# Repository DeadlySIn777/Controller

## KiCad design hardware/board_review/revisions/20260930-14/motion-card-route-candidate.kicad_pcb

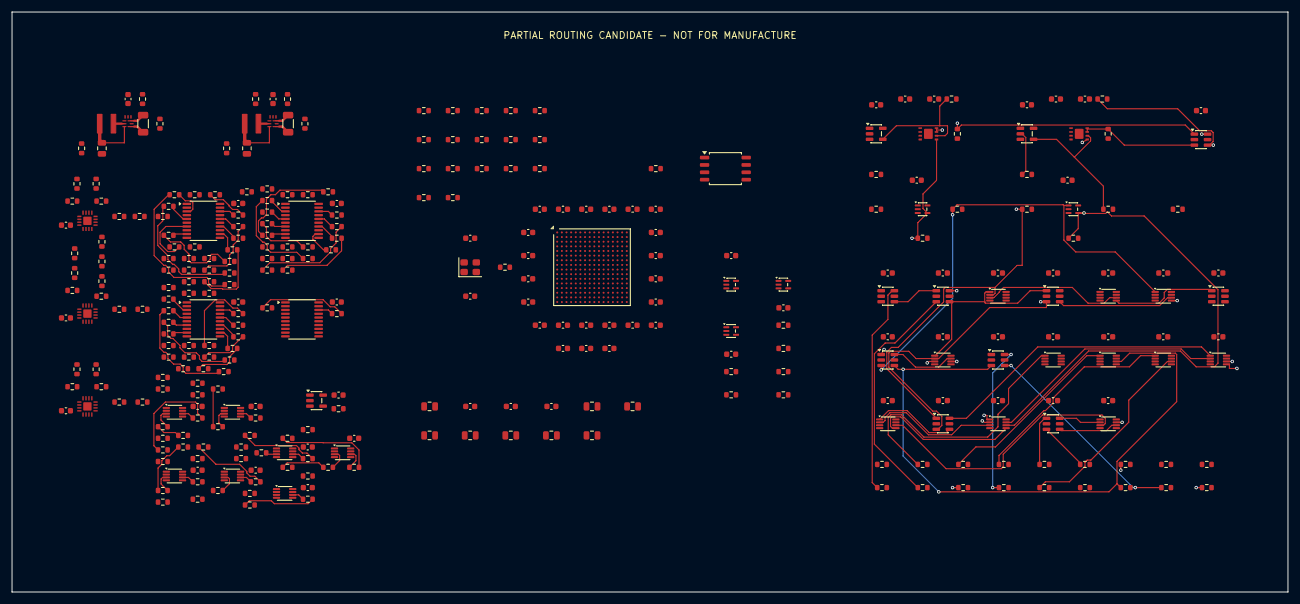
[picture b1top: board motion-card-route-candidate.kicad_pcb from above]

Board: 6 copper layers, 220.0 x 100.0 mm, 327 parts (0 on the bottom side), 203 nets.

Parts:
C1001, C1002, C1003, C1004, C1005, C1006, C1007, C1008, C1009, C1010, C1011, C1012, C1013, C1014, C1015, C1016, C1017, C1018, C1019, C1020, C1021, C1022, C1023, C1035, C1038: 885012206046; C_0603_1608Metric
C1024, C1028, C1029, C1030, C1031, C1032, C1033, C1034: 885012207053; C_0805_2012Metric
C1025, C1026, C1027, C1036, C1039: 885012206052; C_0603_1608Metric
C1037: 885012206040; C_0603_1608Metric
C2001, C2004: C3216X7R1E106K160AB; C_1206_3216Metric
C2002, C2005: C2012X7S1A226M125AC; C_0805_2012Metric
C2003, C2006: GRM1885C1H682JA01D; C_0603_1608Metric
C2007, C2008, C2009, C2010, C3003, C3004, C3005, C3006, C3007, C3008, C3009, C4001, C4002, C4003, C4004, C4005, C4006, C4007, C4008, C4009, C4010, C4011, C4012, C4013, C4014, C4015, C4016, C4017, C4018, C4019, C5001, C5002, C5003, C5004, C5005, C5006, C5007, C5008, C5009, C5010, C5011: GRM188R72A104KA35D; C_0603_1608Metric
C3001, C3002: CL10C332JB8NNNC; C_0603_1608Metric
L2001: XGL4020-222MEC; XGL4020
L2002: XGL4020-102MEC; XGL4020
R1001, R1002, R5001, R5002, R5003, R5004, R5005, R5006, R5007, R5008, R5009, R5010, R5011, R5012, R5013, R5014, R5015, R5016, R5017, R5018, R5019, R5020, R5021, R5022, R5023, R5024, R5025, R5026, R5027, R5028, R5029, R5030, R5031, R5032, R5033, R5034, R5035, R5036, R5037, R5038: CRCW060333R0FKEA; R_0603_1608Metric
R1003, R1004, R1005, R1006, R1007, R1008, R1009, R1010, R1011, R1012, R1013, R1014, R1015, R1016, R1017, R1018, R1019, R1022, R1023, R1024, R1025, R2002, R2006, R2103, R2105, R3001, R3002, R4008, R4009, R4010, R4011, R4012, R4013, R4014, R4015, R4016, R4017, R4018, R5077, R5078, R5079, R5080, R5081, R5082, R5083, R5084, R5085, R5086, R5087, R5088, R5089, R5090, R5091, R5092, R5093, R5094, R5095, R5096, R5097, R5098, R5099, R5100, R5101, R5102: CRCW060310K0FKEA; R_0603_1608Metric
R1020, R2106: CRCW060347K0FKEA; R_0603_1608Metric
R1021: CRCW06031K00FKEA; R_0603_1608Metric
R2001: CRCW060376K8FKEA; R_0603_1608Metric
R2003, R2007, R3006, R3008, R3009, R3010, R3011, R3012: CRCW0603100KFKEA; R_0603_1608Metric
R2005: CRCW060332K4FKEA; R_0603_1608Metric
R2008: CRCW0603301KFKEA; R_0603_1608Metric
R2021: PLT0603Z8792LST1; R_0603_1608Metric
R2027, R2035, R2067, R2075: PLT0603Z1002LST1; R_0603_1608Metric
R2029: PLT0603Z9212LST1; R_0603_1608Metric
R2041: PLT0603Z1071LST1; R_0603_1608Metric
R2042: PLT0603Z2610LST1; R_0603_1608Metric
R2047, R2055: PLT0603Z1001LST1; R_0603_1608Metric
R2049: PLT0603Z1151LST1; R_0603_1608Metric
R2050: PLT0603Z3160LST1; R_0603_1608Metric
R2051: CRCW06034R02FKEA; R_0603_1608Metric
R2061: PLT0603Z5452LST1; R_0603_1608Metric
R2069: PLT0603Z5752LST1; R_0603_1608Metric
R2101, R2102: CRCW06033K30FKEA; R_0603_1608Metric
R2104: CRCW06036K80FKEA; R_0603_1608Metric
R2107: CRCW0603470KFKEA; R_0603_1608Metric
R2108, R3003, R3004, R3005, R3007, R3013, R4001, R4002, R4003, R4004, R4005, R4006, R4007, R5039, R5040, R5041, R5042, R5043, R5044, R5045, R5046, R5047, R5048, R5049, R5050, R5051, R5052, R5053, R5054, R5055, R5056, R5057, R5058, R5059, R5060, R5061, R5062, R5063, R5064, R5065, R5066, R5067, R5068, R5069, R5070, R5071, R5072, R5073, R5074, R5075, R5076: CRCW06034K70FKEA; R_0603_1608Metric
U1001: T20F256I4; T20F256_Efinix_NSMD
U1002: W25Q32JVSSIQ; SOIC-8_5.3x5.3mm_P1.27mm
U1003, U1005, U3006, U3007: SN74LVC1G08DCKR; SOT-353_SC-70-5
U1004: 74LVC1G17GW; SOT-353_SC-70-5
U2001, U2002: TPS62901RPJR; TPS62901_RPJ9
U2003, U2004, U2005: LTC2962HUD#PBF; LTC2962_UD16
U2006: SN74LVC1G17DBVR; SOT-23-5
U3001, U3002: TPS3851G18SDRBT; TPS3851_DRB8
U3003, U3004: SN74LVC1G34DBVR; SOT-23-5
U3005: SN74LVC2G17DBVR; SOT-23-6
U4001, U4002, U4004, U4007, U4008, U4010: SN74LVC1G11DBVR; SOT-23-6
U4003, U4009, U4019: SN74LVC2G08DCUR; VSSOP-8_2.3x2mm_P0.5mm
U4005, U4006, U4011, U4012, U4013, U4014, U4015: SN74LVC2G74DCUR; VSSOP-8_2.3x2mm_P0.5mm
U4016, U4018: SN74LVC2G04DBVR; SOT-23-6
U4017: SN74LVC2G32DCUR; VSSOP-8_2.3x2mm_P0.5mm
U5001, U5002, U5003, U5004: SN74LVC244APWR; TSSOP-20_4.4x6.5mm_P0.65mm
U5005, U5006, U5007, U5008, U5009, U5010, U5011: SN74LVC2G126DCUR; VSSOP-8_2.3x2mm_P0.5mm
Y1001: ASE-50.000MHZ-L-C-T; Oscillator_SMD_Abracon_ASE-4Pin_3.2x2.5mm

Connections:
/BANK_B_BUFFER_ENABLE_QUALIFIED: R4014.1, R5076.1, U4013.6, U5005.1, U5005.7, U5006.1, U5006.7, U5007.1, U5007.7, U5008.1, U5008.7, U5009.1, U5009.7, U5010.1, U5010.7, U5011.1
/CORE_1V2: C1001.1, C1002.1, C1003.1, C1004.1, C1005.1, C1006.1, C1007.1, C1008.1, C1009.1, C1024.1, C1025.1, C1026.1, C1027.1, C2002.1, L2001.2, R2003.1, R2041.1, R2049.1, U1001.E9, U1001.F7, U1001.F8, U1001.F9, U1001.G11, U1001.J6, U1001.J7, U1001.K9, U1001.K11, U2001.3
/DIR0_FPGA: R5040.1, U1001.J5, U5001.4
/DIR1_FPGA: R5042.1, U1001.K3, U5001.11
/DIR2_FPGA: R5044.1, U1001.K1, U5001.17
/DIR3_FPGA: R5046.1, U1001.H1, U5002.6
/DIR4_FPGA: R5048.1, U1001.H2, U5002.13
/DIR5_FPGA: R5050.1, U1001.G3, U5003.2
/DIR6_FPGA: R5052.1, U1001.G2, U5003.8
/DIR7_FPGA: R5054.1, U1001.C1, U5003.15
/DIR8_FPGA: R5056.1, U1001.F3, U5005.5
/DIR9_FPGA: R5058.1, U1001.E1, U5007.2
/DIR10_FPGA: R5060.1, U1001.G4, U5008.5
/DIR11_FPGA: R5062.1, U1001.B1, U5010.2
/EN0_N_FPGA: R5063.1, U1001.H12, U5001.6
/EN1_N_FPGA: R5064.1, U1001.J12, U5001.13
/EN2_N_FPGA: R5065.1, U1001.L16, U5002.2
/EN3_N_FPGA: R5066.1, U1001.M15, U5002.8
/EN4_N_FPGA: R5067.1, U1001.M16, U5002.15
/EN5_N_FPGA: R5068.1, U1001.P16, U5003.4
/EN6_N_FPGA: R5069.1, U1001.L15, U5003.11
/EN7_N_FPGA: R5070.1, U1001.K12, U5003.17
/EN8_N_FPGA: R5071.1, U1001.N14, U5006.2
/EN9_N_FPGA: R5072.1, U1001.N16, U5007.5
/EN10_N_FPGA: R5073.1, U1001.P15, U5009.2
/EN11_N_FPGA: R5074.1, U1001.M14, U5010.5
/FPGA_CRESET_N: R2108.1, R4008.1, U1003.1, U2006.4, U4001.1, U4019.1, U4019.5
/FPGA_ENDPOINT_READY: R1023.1, R4001.1, U1001.C4, U4003.6, U4004.6
/FPGA_MOTION_REQUEST: R1024.1, R3003.1, U1001.B3, U3006.1, U4005.1, U4007.3
/FPGA_OUTPUT_REQUEST: R3004.1, U3007.1, U4006.1, U4008.3
/FPGA_PROGRESS_M: R1025.1, R3005.1, U1001.E4, U3003.2
/FPGA_USER_RESET_N: R3013.1, R4009.1, U1001.D5, U1005.4, U3006.2, U3007.2, U4001.3
/IO_3V3: C1010.1, C1011.1, C1012.1, C1013.1, C1014.1, C1015.1, C1016.1, C1017.1, C1018.1, C1019.1, C1020.1, C1021.1, C1022.1, C1023.1, C1028.1, C1029.1, C1030.1, C1031.1, C1032.1, C1033.1, C1034.1, C1035.1, C1036.1, C1037.1, C1038.1, C2005.1, C2010.1, C3003.1, C3004.1, C3005.1, C3006.1, C3007.1, C3008.1, C3009.1, C4001.1, C4002.1, C4003.1, C4004.1, C4005.1, C4006.1, C4007.1, C4008.1, C4009.1, C4010.1, C4011.1, C4012.1, C4013.1, C4014.1, C4015.1, C4016.1, C4017.1, C4018.1, C4019.1, C5001.1, C5002.1, C5003.1, C5004.1, C5005.1, C5006.1, C5007.1, C5008.1, C5009.1, C5010.1, C5011.1, L2002.2, R1003.1, R1004.1, R1005.1, R1006.1, R1007.1, R1008.1, R1009.1, R1010.1, R1011.1, R1012.1, R1013.1, R1014.1, R1015.1, R1016.1, R1017.1, R1020.1, R2007.1, R2061.1, R2069.1, R3001.1, R3002.1, R5063.2, R5064.2, R5065.2, R5066.2, R5067.2, R5068.2, R5069.2, R5070.2, R5071.2, R5072.2, R5073.2, R5074.2, U1001.E10, U1001.F6, U1001.F10, U1001.F11, U1001.G6, U1001.H6, U1001.H7, U1001.J10, U1001.J11, U1001.K6, U1001.L6, U1001.L7, U1001.L10, U1001.L11, U1002.8, U1003.5, U1004.5, U1005.5, U2002.3, U2006.5, U3001.1, U3002.1, U3003.5, U3004.5, U3005.5, U3006.5, U3007.5, U4001.5, U4002.5, U4003.8, U4004.5, U4005.2, U4005.7, U4005.8, U4006.2, U4006.7, U4006.8, U4007.5, U4008.5, U4009.8, U4010.5, U4011.2, U4011.7, U4011.8, U4012.2, U4012.7, U4012.8, U4013.2, U4013.7, U4013.8, U4014.7, U4014.8, U4015.7, U4015.8, U4016.5, U4017.8, U4018.5, U4019.8, U5001.20, U5002.20, U5003.20, U5004.20, U5005.8, U5006.8, U5007.8, U5008.8, U5009.8, U5010.8, U5011.8, Y1001.1, Y1001.4
/LOGIC_GND: C1001.2, C1002.2, C1003.2, C1004.2, C1005.2, C1006.2, C1007.2, C1008.2, C1009.2, C1010.2, C1011.2, C1012.2, C1013.2, C1014.2, C1015.2, C1016.2, C1017.2, C1018.2, C1019.2, C1020.2, C1021.2, C1022.2, C1023.2, C1024.2, C1025.2, C1026.2, C1027.2, C1028.2, C1029.2, C1030.2, C1031.2, C1032.2, C1033.2, C1034.2, C1035.2, C1036.2, C1037.2, C1038.2, C1039.2, C2001.2, C2002.2, C2003.2, C2004.2, C2005.2, C2006.2, C2007.2, C2008.2, C2009.2, C2010.2, C3001.2, C3002.2, C3003.2, C3004.2, C3005.2, C3006.2, C3007.2, C3008.2, C3009.2, C4001.2, C4002.2, C4003.2, C4004.2, C4005.2, C4006.2, C4007.2, C4008.2, C4009.2, C4010.2, C4011.2, C4012.2, C4013.2, C4014.2, C4015.2, C4016.2, C4017.2, C4018.2, C4019.2, C5001.2, C5002.2, C5003.2, C5004.2, C5005.2, C5006.2, C5007.2, C5008.2, C5009.2, C5010.2, C5011.2, R1018.2, R1019.2, R1021.2, R1023.2, R1024.2, R1025.2, R2001.2, R2002.2, R2003.2, R2005.2, R2006.2, R2007.2, R2008.2, R2027.2, R2035.2, R2047.2, R2055.2, R2067.2, R2075.2, R2103.2, R2105.2, R2107.2, R2108.2, R3003.2, R3004.2, R3005.2, R3006.2, R3007.2, R3008.2, R3009.2, R3010.2, R3011.2, R3012.2, R3013.2, R4001.2, R4002.2, R4003.2, R4004.2, R4005.2, R4006.2, R4007.2, R4008.2, R4009.2, R4010.2, R4011.2, R4012.2, R4013.2, R4014.2, R4015.2, R4016.2, R4017.2, R4018.2, R5039.2, R5040.2, R5041.2, R5042.2, R5043.2, R5044.2, R5045.2, R5046.2, R5047.2, R5048.2, R5049.2, R5050.2, R5051.2, R5052.2, R5053.2, R5054.2, R5055.2, R5056.2, R5057.2, R5058.2, R5059.2, R5060.2, R5061.2, R5062.2, R5075.2, R5076.2, R5077.2, R5078.2, R5079.2, R5080.2, R5081.2, R5082.2, R5083.2, R5084.2, R5085.2, R5086.2, R5087.2, R5088.2, R5089.2, R5090.2, R5091.2, R5092.2, R5093.2, R5094.2, R5095.2, R5096.2, R5097.2, R5098.2, R5099.2, R5100.2, R5101.2, R5102.2, U1001.A1, U1001.A5, U1001.A12, U1001.A16, U1001.D2, U1001.D15, U1001.G7, U1001.G8, U1001.G9, U1001.G10, U1001.H8, U1001.H9, U1001.H10, U1001.H11, U1001.J1, U1001.J8, U1001.J9, U1001.J16, U1001.K7, U1001.K8, U1001.K10, U1001.L8, U1001.L9, U1001.N2, U1001.N15, U1001.R7, U1001.R10, U1001.T1, U1001.T4, U1001.T13, U1001.T16, U1002.4, U1003.3, U1004.3, U1005.3, U2001.4, U2001.9, U2002.4, U2003.3, U2003.7, U2003.11, U2003.17, U2004.3, U2004.7, U2004.11, U2004.17, U2005.3, U2005.7, U2005.11, U2005.17, U2006.3, U3001.4, U3001.9, U3002.4, U3002.9, U3003.3, U3004.3, U3005.2, U3006.3, U3007.3, U4001.2, U4002.2, U4003.4, U4004.2, U4005.4, U4006.4, U4007.2, U4008.2, U4009.4, U4010.2, U4011.4, U4012.4, U4013.4, U4014.4, U4015.4, U4016.2, U4017.4, U4018.2, U4019.4, U5001.1, U5001.10, U5001.19, U5002.1, U5002.10, U5002.19, U5003.1, U5003.10, U5003.19, U5004.1, U5004.4, U5004.6, U5004.8, U5004.10, U5004.11, U5004.13, U5004.15, U5004.17, U5004.19, U5005.4, U5006.4, U5007.4, U5008.4, U5009.4, U5010.4, U5011.4, U5011.5, U5011.7, Y1001.2
/RAW_INHIBIT_N: U1001.A2, U4003.5, U4003.7, U4007.6
/STEP0_FPGA: R5039.1, U1001.P2, U5001.2
/STEP1_FPGA: R5041.1, U1001.J4, U5001.8
/STEP2_FPGA: R5043.1, U1001.J3, U5001.15
/STEP3_FPGA: R5045.1, U1001.K2, U5002.4
/STEP4_FPGA: R5047.1, U1001.L1, U5002.11
/STEP5_FPGA: R5049.1, U1001.H4, U5002.17
/STEP6_FPGA: R5051.1, U1001.G5, U5003.6
/STEP7_FPGA: R5053.1, U1001.F1, U5003.13
/STEP8_FPGA: R5055.1, U1001.E2, U5005.2
/STEP9_FPGA: R5057.1, U1001.D1, U5006.5
/STEP10_FPGA: R5059.1, U1001.E3, U5008.2
/STEP11_FPGA: R5061.1, U1001.F4, U5009.5
/TX_PERMIT: R4015.1, R5075.1, U1001.E6, U4007.4, U4009.5, U4010.1, U4011.6, U5004.2, U5011.2
/WD_M_OK: R3009.1, U3005.6, U4003.2, U4016.1
/WD_M_SET1_BUF: R3011.1, U3001.5, U3006.4, U4017.2
/WD_O_OK: R3010.1, U3005.4, U4004.3, U4009.2, U4016.3
/WD_O_SET1_BUF: R3012.1, U3002.5, U3007.4, U4017.6
/fpga_core/FPGA_CDONE: R1003.2, R1022.1, U1001.R1
/fpga_core/FPGA_CFG_CBSEL0: R1018.1, U1001.C7
/fpga_core/FPGA_CFG_CBSEL1: R1019.1, U1001.D7
/fpga_core/FPGA_CFG_CBUS0: R1009.2, U1001.K13
/fpga_core/FPGA_CFG_CBUS1: R1008.2, U1001.L14
/fpga_core/FPGA_CFG_CBUS2: R1007.2, U1001.R16
/fpga_core/FPGA_CFG_CSI: R1004.2, U1001.N3
/fpga_core/FPGA_CFG_NSTATUS: R1017.2, U1001.B8
/fpga_core/FPGA_CFG_TEST_N: R1005.2, U1001.L12
/fpga_core/FPGA_CLK_50M: R1001.2, U1001.H3
/fpga_core/FPGA_CLK_SOURCE: R1001.1, Y1001.3
/fpga_core/FPGA_FLASH_CCK: R1002.2, U1002.6
/fpga_core/FPGA_FLASH_CCK_SOURCE: R1002.1, U1001.M3
/fpga_core/FPGA_FLASH_CS_N: R1006.2, U1001.P3, U1002.1
/fpga_core/FPGA_FLASH_IO2: R1014.2, U1002.3
/fpga_core/FPGA_FLASH_IO3: R1015.2, U1002.7
/fpga_core/FPGA_FLASH_MISO: U1001.N1, U1002.2
/fpga_core/FPGA_FLASH_MOSI: U1001.L3, U1002.5
/fpga_core/FPGA_JTAG_TCK: R1010.2, U1001.M2
/fpga_core/FPGA_JTAG_TDI: R1011.2, U1001.K5
/fpga_core/FPGA_JTAG_TDO: R1013.2, U1001.L5
/fpga_core/FPGA_JTAG_TMS: R1012.2, U1001.M1
/fpga_core/FPGA_LOCAL_RESET_N: R1020.2, R1021.1, U1001.P1, U1003.4
/fpga_core/FPGA_SERVICE_RUN_N: R1016.2, U1003.2, U1005.2
/fpga_core/FPGA_USER_RESET_DELAYED: U1004.4, U1005.1
/fpga_core/FPGA_USER_RESET_RC: C1039.1, R1022.2, U1004.2
/mc_local_power/CORE_1V2_EN: R2002.1, R2102.2, R2103.1, U2001.5
/mc_local_power/CORE_1V2_MODE: R2001.1, U2001.7
/mc_local_power/CORE_1V2_OV_SENSE: R2051.2, R2055.1, U2004.15
/mc_local_power/CORE_1V2_SS: C2003.1, U2001.8
/mc_local_power/CORE_1V2_SW: L2001.1, U2001.2
/mc_local_power/CORE_1V2_UV_SENSE: R2042.2, R2047.1, U2004.16
/mc_local_power/CORE_5V: C2001.1, C2004.1, C2007.1, C2008.1, C2009.1, R2021.1, R2029.1, R2101.1, R2104.1, R2106.1, U2001.6, U2002.6, U2003.1, U2003.2, U2003.4, U2003.10, U2003.13, U2003.14, U2004.1, U2004.4, U2004.10, U2004.13, U2004.14, U2005.1, U2005.4, U2005.10, U2005.13, U2005.14
/mc_local_power/CORE_5V_OV_SENSE: R2029.2, R2035.1, U2003.15
/mc_local_power/CORE_5V_UV_SENSE: R2021.2, R2027.1, U2003.16
/mc_local_power/IO_3V3_EN: R2006.1, R2104.2, R2105.1, U2002.5, U2004.12, U2005.2
/mc_local_power/IO_3V3_MODE: R2005.1, U2002.7
/mc_local_power/IO_3V3_OV_SENSE: R2069.2, R2075.1, U2005.15
/mc_local_power/IO_3V3_SS: C2006.1, U2002.8
/mc_local_power/IO_3V3_SW: L2002.1, U2002.2
/mc_local_power/IO_3V3_UV_SENSE: R2061.2, R2067.1, U2005.16
/mc_local_power/IO_3V3_VSET: R2008.1, U2002.9
/mc_local_power/MC_RAILS_OK_5V: R2106.2, R2107.1, U2005.12, U2006.2
/mc_local_power/MC_SEQ_5V_OK: R2101.2, R2102.1, U2003.12, U2004.2
/mc_local_power/MC_SEQ_OV2_1: R2049.2, R2050.1
/mc_local_power/MC_SEQ_OV2_2: R2050.2, R2051.1
/mc_local_power/MC_SEQ_REF1: U2003.5, U2003.6, U2003.8, U2003.9
/mc_local_power/MC_SEQ_REF2: U2004.5, U2004.6, U2004.8, U2004.9
/mc_local_power/MC_SEQ_REF3: U2005.5, U2005.6, U2005.8, U2005.9
/mc_local_power/MC_SEQ_UV2_1: R2041.2, R2042.1
/mc_motor_buffers/DIR0_BUFFER_OUT: R5002.1, U5001.16
/mc_motor_buffers/DIR0_TO_MIA: R5002.2, R5078.1
/mc_motor_buffers/DIR1_BUFFER_OUT: R5005.1, U5001.9
/mc_motor_buffers/DIR1_TO_MIA: R5005.2, R5080.1
/mc_motor_buffers/DIR2_BUFFER_OUT: R5008.1, U5001.3
/mc_motor_buffers/DIR2_TO_MIA: R5008.2, R5082.1
/mc_motor_buffers/DIR3_BUFFER_OUT: R5011.1, U5002.14
/mc_motor_buffers/DIR3_TO_MIA: R5011.2, R5084.1
/mc_motor_buffers/DIR4_BUFFER_OUT: R5014.1, U5002.7
/mc_motor_buffers/DIR4_TO_MIA: R5014.2, R5086.1
/mc_motor_buffers/DIR5_BUFFER_OUT: R5017.1, U5003.18
/mc_motor_buffers/DIR5_TO_MIA: R5017.2, R5088.1
/mc_motor_buffers/DIR6_BUFFER_OUT: R5020.1, U5003.12
/mc_motor_buffers/DIR6_TO_MIA: R5020.2, R5090.1
/mc_motor_buffers/DIR7_BUFFER_OUT: R5023.1, U5003.5
/mc_motor_buffers/DIR7_TO_MIA: R5023.2, R5092.1
/mc_motor_buffers/DIR8_BUFFER_OUT: R5026.1, U5005.3
/mc_motor_buffers/DIR8_TO_MX4: R5026.2, R5094.1
/mc_motor_buffers/DIR9_BUFFER_OUT: R5029.1, U5007.6
/mc_motor_buffers/DIR9_TO_MX4: R5029.2, R5096.1
/mc_motor_buffers/DIR10_BUFFER_OUT: R5032.1, U5008.3
/mc_motor_buffers/DIR10_TO_MX4: R5032.2, R5098.1
/mc_motor_buffers/DIR11_BUFFER_OUT: R5035.1, U5010.6
/mc_motor_buffers/DIR11_TO_MX4: R5035.2, R5100.1
/mc_motor_buffers/EN0_N_BUFFER_OUT: R5003.1, U5001.14
/mc_motor_buffers/EN1_N_BUFFER_OUT: R5006.1, U5001.7
/mc_motor_buffers/EN2_N_BUFFER_OUT: R5009.1, U5002.18
/mc_motor_buffers/EN3_N_BUFFER_OUT: R5012.1, U5002.12
/mc_motor_buffers/EN4_N_BUFFER_OUT: R5015.1, U5002.5
/mc_motor_buffers/EN5_N_BUFFER_OUT: R5018.1, U5003.16
/mc_motor_buffers/EN6_N_BUFFER_OUT: R5021.1, U5003.9
/mc_motor_buffers/EN7_N_BUFFER_OUT: R5024.1, U5003.3
/mc_motor_buffers/EN8_N_BUFFER_OUT: R5027.1, U5006.6
/mc_motor_buffers/EN9_N_BUFFER_OUT: R5030.1, U5007.3
/mc_motor_buffers/EN10_N_BUFFER_OUT: R5033.1, U5009.6
/mc_motor_buffers/EN11_N_BUFFER_OUT: R5036.1, U5010.3
/mc_motor_buffers/STEP0_BUFFER_OUT: R5001.1, U5001.18
/mc_motor_buffers/STEP0_TO_MIA: R5001.2, R5077.1
/mc_motor_buffers/STEP1_BUFFER_OUT: R5004.1, U5001.12
/mc_motor_buffers/STEP1_TO_MIA: R5004.2, R5079.1
/mc_motor_buffers/STEP2_BUFFER_OUT: R5007.1, U5001.5
/mc_motor_buffers/STEP2_TO_MIA: R5007.2, R5081.1
/mc_motor_buffers/STEP3_BUFFER_OUT: R5010.1, U5002.16
/mc_motor_buffers/STEP3_TO_MIA: R5010.2, R5083.1
/mc_motor_buffers/STEP4_BUFFER_OUT: R5013.1, U5002.9
/mc_motor_buffers/STEP4_TO_MIA: R5013.2, R5085.1
/mc_motor_buffers/STEP5_BUFFER_OUT: R5016.1, U5002.3
/mc_motor_buffers/STEP5_TO_MIA: R5016.2, R5087.1
/mc_motor_buffers/STEP6_BUFFER_OUT: R5019.1, U5003.14
/mc_motor_buffers/STEP6_TO_MIA: R5019.2, R5089.1
/mc_motor_buffers/STEP7_BUFFER_OUT: R5022.1, U5003.7
/mc_motor_buffers/STEP7_TO_MIA: R5022.2, R5091.1
/mc_motor_buffers/STEP8_BUFFER_OUT: R5025.1, U5005.6
/mc_motor_buffers/STEP8_TO_MX4: R5025.2, R5093.1
/mc_motor_buffers/STEP9_BUFFER_OUT: R5028.1, U5006.3
/mc_motor_buffers/STEP9_TO_MX4: R5028.2, R5095.1
/mc_motor_buffers/STEP10_BUFFER_OUT: R5031.1, U5008.6
/mc_motor_buffers/STEP10_TO_MX4: R5031.2, R5097.1
/mc_motor_buffers/STEP11_BUFFER_OUT: R5034.1, U5009.3
/mc_motor_buffers/STEP11_TO_MX4: R5034.2, R5099.1
/mc_motor_buffers/TX_PERMIT_A_BUFFER_OUT: R5037.1, U5004.18
/mc_motor_buffers/TX_PERMIT_A_TO_MIA: R5037.2, R5101.1
/mc_motor_buffers/TX_PERMIT_B_BUFFER_OUT: R5038.1, U5011.6
/mc_motor_buffers/TX_PERMIT_B_TO_MX4: R5038.2, R5102.1
/mc_permission/ARM_M_Q: U4005.5, U4007.1
/mc_permission/ARM_O_Q: U4006.5, U4008.1
/mc_permission/BASE_FIRST: U4001.4, U4002.1
/mc_permission/BASE_OK: U4002.4, U4003.1, U4004.1, U4009.1
/mc_permission/DIC_OK_QUALIFIED: R4010.1, U4001.6
/mc_permission/EXT_PERMIT_3V3: R4011.1, U4002.3
/mc_permission/LATCH_CLEAR_M_N: U4003.3, U4005.6
/mc_permission/LATCH_CLEAR_O_N: U4004.4, U4006.6
/mc_permission/OPI_REARM_BOE: R4004.1, U4013.1
/mc_permission/OPI_REARM_OUT: R4003.1, U4012.1
/mc_permission/OPI_REARM_TX: R4002.1, U4011.1
/mc_permission/OUTPUT_RAW_OK: U4008.6, U4009.7
/mc_permission/OUT_PERMIT: R4016.1, U4008.4, U4010.3, U4012.6
/mc_permission/PERMIT_OUT_DRIVE: R4018.1, U4009.3
/mc_permission/PERMIT_OUT_REQ: R4007.1, U4009.6
/mc_permission/PROCESS_PERMIT_EXT_3V3: R4013.1, U4010.6
/mc_permission/PROC_PERMIT: R4017.1, U4010.4
/mc_permission/TAMPER_CLEAR_N: R4012.1, U4002.6
/mc_permission/WD_M_FALL_CLK: U4014.1, U4016.6
/mc_permission/WD_M_RECORD_CLEAR_N: U4018.6, U4019.2
/mc_permission/WD_M_TRIP_CLEAR_N: U4014.6, U4019.7
/mc_permission/WD_M_TRIP_D: U4014.2, U4017.7
/mc_permission/WD_M_TRIP_Q: U4014.5, U4017.1
/mc_permission/WD_O_FALL_CLK: U4015.1, U4016.4
/mc_permission/WD_O_RECORD_CLEAR_N: U4018.4, U4019.6
/mc_permission/WD_O_TRIP_CLEAR_N: U4015.6, U4019.3
/mc_permission/WD_O_TRIP_D: U4015.2, U4017.3
/mc_permission/WD_O_TRIP_Q: U4015.5, U4017.5
/mc_permission/WD_REARM_M: R4005.1, U4018.1
/mc_permission/WD_REARM_O: R4006.1, U4018.3
/watchdog_conditioning/FPGA_PROGRESS_O: R3007.1, U3004.2
/watchdog_conditioning/WD_M_CWD: C3001.1, U3001.2
/watchdog_conditioning/WD_M_HEALTH_RAW: R3001.2, U3001.7, U3001.8, U3005.1
/watchdog_conditioning/WD_M_WDI_BUF: R3006.1, U3001.6, U3003.4
/watchdog_conditioning/WD_O_CWD: C3002.1, U3002.2
/watchdog_conditioning/WD_O_HEALTH_RAW: R3002.2, U3002.7, U3002.8, U3005.3
/watchdog_conditioning/WD_O_WDI_BUF: R3008.1, U3002.6, U3004.4
